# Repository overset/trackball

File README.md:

## Trackball Mezzanine PCBs

These are the mezzanine PCBs that connect the <a href="https://www.adafruit.com/product/4600">Adafruit QT Py</a> (SAMD21) MCU, <a href="https://github.com/mrjohnk/PMW3389DM">MrJohnK PMW3389</a> optical sensor breakout (<a href="https://www.tindie.com/products/jkicklighter/pmw3389-motion-sensor/">available on Tindie as of 2022</a>), simple components for the haptic feedback motor and pads for capacitive pickup wiring. This PCB allows for easy mounting inside the case for most components as well as a ground plane to help with the capacitive pickup interference. These are simple 2-layer PCBs that made with KiCad6 and includes a few custom footprints/symbols for the haptic motor. These can easily be fabricated through OSHPark, JLCPCB, etc. Original prototypes were fabricated by OSHPark and the gerber & hole files were exported from KiCad6 with OSHPark guidelines.

### Dual Optical Sensor PCB

*Currently work in progress*

This mezzanine PCB supports 2 optical sensor breakout boards being tested on a new case design. This leverages the PMW3389DM-T3QU or PMW3360DM-T2QU breakout boards from MrJohnK. Having the second optical sensor enables detecting horizontal ball movement (like a flat spin) to enable scroll/wheel events. This is specifically designed to work with the current case design detecting movements off a radial ball bearing for 1 sensor (scroll) and the trackball itself (x, y cursor movement).

<p align="center">
	<span align="left"></span>
	<span align="left"></span>
	<span align="left"></span>
	<span align="right"></span>
</p>

### Single Optical Sensor PCB

This mezzanine PCB supports a single optical sensor breakout and is good for a dedicated trackball or dedicated scrollball. This allows for a smaller case design, but made with using a 50mm or larger ball.

<p align="center">
	<span align="left"></span>
	<span align="left"></span>
	<span align="right"></span>
</p>

Assembly of the first print:

<p align="center">
	<span align="left"></span>
	<span align="left"></span>
	<span align="right"></span>
</p>

## Credits, Attribution and Inspiration

* <a href="https://github.com/monroewilliams/trackball">MonroeWilliams' Trackball</a> project
* <a href="https://github.com/jfedor2">jfedor2's multiple trackball</a> projects

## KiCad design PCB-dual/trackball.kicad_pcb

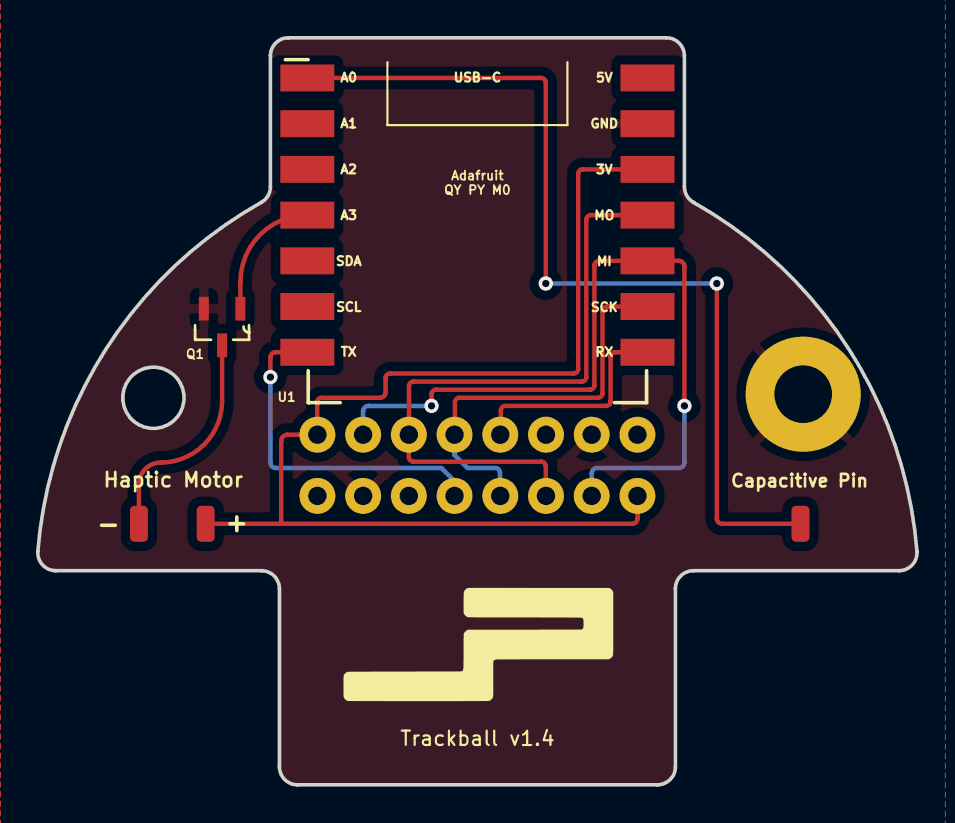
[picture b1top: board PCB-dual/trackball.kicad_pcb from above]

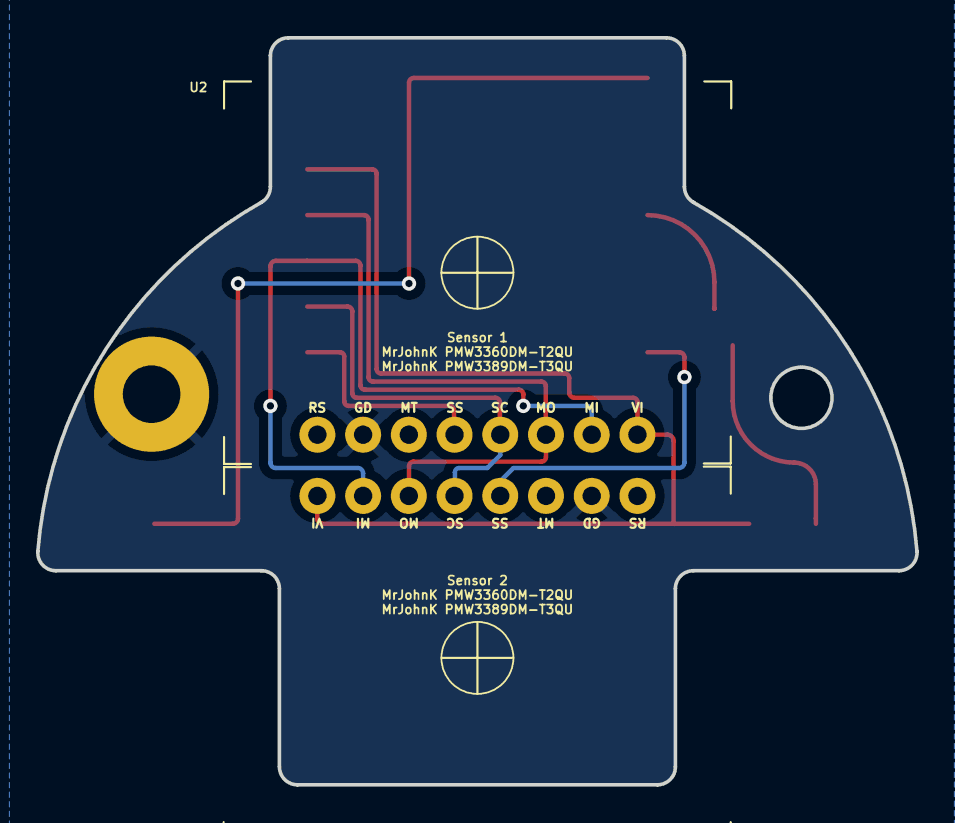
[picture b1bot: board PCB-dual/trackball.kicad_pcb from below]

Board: 2 copper layers, 48.8 x 41.5 mm, 8 parts (2 on the bottom side), 10 nets.

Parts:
+: Conn_01x01_Male; SolderWirePad_1x01_SMD_1x2mm
-: Conn_01x01_Male; SolderWirePad_1x01_SMD_1x2mm
H1: MountingHole_Pad; MountingHole_3.2mm_M3_Pad
J3: Conn_01x01_Male; SolderWirePad_1x01_SMD_1x2mm
Q1: MMBT2222A-7-F
U1: Adafruit_QT_Py_M0; Adafruit_QT_PY_M0
U2, U3: MrJohnK_PMW3360DM-T2QU

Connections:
unnamed: +.1, U1.10 (3V), U2.8 (VI), U3.8 (VI)
unnamed: -.1, Q1.3 (C)
unnamed: J3.1, U1.1 (A0)
unnamed: Q1.1 (B), U1.4 (A3)
unnamed: H1.1, Q1.2 (E), U1.9 (GND), U2.2 (GD), U3.2 (GD)
unnamed: U1.7 (TX), U3.4 (SS)
unnamed: U1.11 (MO), U2.6 (MO), U3.6 (MO)
unnamed: U1.12 (MI), U2.7 (MI), U3.7 (MI)
unnamed: U1.13 (SCK), U2.5 (SC), U3.5 (SC)
unnamed: U1.14 (RX), U2.4 (SS)

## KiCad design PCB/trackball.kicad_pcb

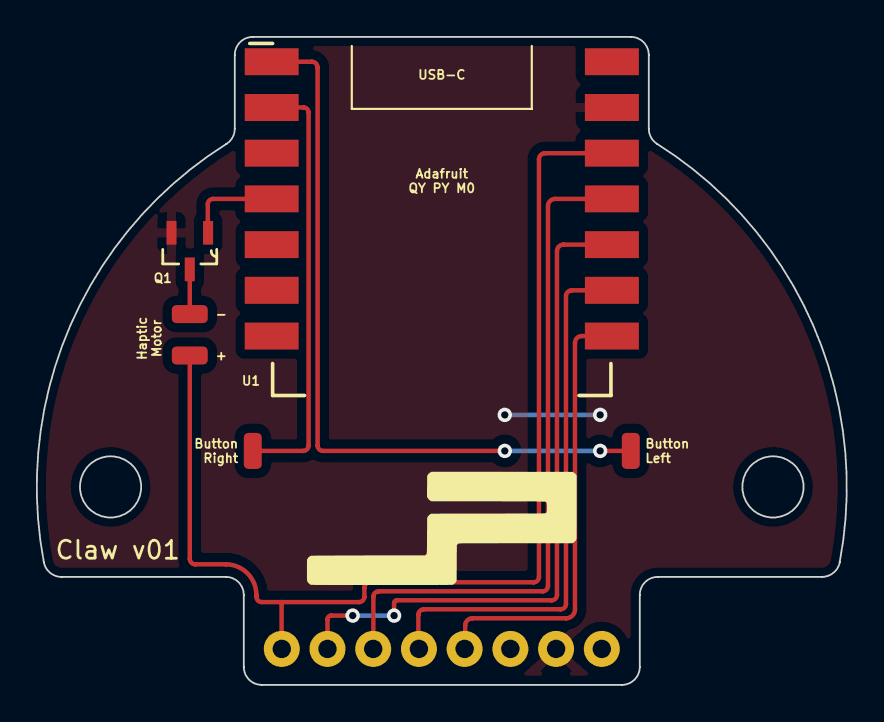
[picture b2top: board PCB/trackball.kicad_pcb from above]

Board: 2 copper layers, 45.0 x 36.0 mm, 7 parts (1 on the bottom side), 10 nets.

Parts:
+: Conn_01x01_Male; SolderWirePad_1x01_SMD_1x2mm
-: Conn_01x01_Male; SolderWirePad_1x01_SMD_1x2mm
J1, J2: Conn_01x01_Male; SolderWirePad_1x01_SMD_1x2mm
Q1: MMBT2222A-7-F
U1: Adafruit_QT_Py_M0; Adafruit_QT_PY_M0
U2: MrJohnK_PMW3360DM-T2QU

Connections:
GND: Q1.2 (E), U1.9 (GND), U2.2 (GD)
unnamed: +.1, U1.10 (3V), U2.8 (VI)
unnamed: -.1, Q1.3 (C)
unnamed: Q1.1 (B), U1.4 (A3)
unnamed: J1.1, U1.1 (A0)
unnamed: J2.1, U1.2 (A1)
unnamed: U1.11 (MO), U2.6 (MO)
unnamed: U1.12 (MI), U2.7 (MI)
unnamed: U1.13 (SCK), U2.5 (SC)
unnamed: U1.14 (RX), U2.4 (SS)

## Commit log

2022-12-16 feat: initial commit
2022-12-16 feat: added initial v01 KiCad6 project files and first pictures of mezzanine PCB
2022-12-16 feat: added v01 build pictures with mezzanine PCB, QT Py and PMW3389 breakout
2022-12-16 bug: capacitive pickup, not haptic pickup
2022-12-17 docs: tweak table for image scaling
2022-12-17 docs: added links to breakouts, attributions and dual vs single PCB outline
2022-12-17 feat: move PCB to PCB-single to differentiate single vs dual sensor PCBs
2022-12-17 docs: add more details for included gerbers and OSHPark preferences
2022-12-18 feat: add WIP for dual sensor PCB. Edge cut works with current 3D model geometry, footprints updated with more silkscreen adds. Just about to begin re-wiring the pads.
2022-12-18 feat: first draft of v02 trackball with dual sensor support, fixes to footprints and OSHPark gerber .zip not yet tested
2022-12-18 docs: quick intro with images for the draft dual sensor mezzanine PCB
2022-12-19 docs: typos on breakout boards sensor IDs
2022-12-19 feat: cleaned up tracks minimizing crossover on F/B layers, simplified some tracks, ground plane now on both sides
2022-12-19 docs: updated v02 PCB editor view and 3D front/back images
2022-12-19 docs: dual sensor to the top of the list
2022-12-19 docs: nuke github html table borders
2022-12-19 docs: nuke github html table borders attempt #2
2022-12-19 docs: cleaner markdown+html grid and renamed dual sensor pictures to correct timestamp
2022-12-19 docs: make the img's float correctly
2022-12-19 docs: center the floating image grids
2022-12-21 feat: added 3D models for QT Py and diode to existing project footprints
2022-12-21 bug: add .step files for updated footprints
2022-12-21 feat: new v03 with new mounting hole placement and proper placement of second sensor with fitment in 55mm sphere sized case
2022-12-21 feat: tweak to silkscreen
2022-12-21 docs: added v03 dual sensor docs, step file from KiCad6
2022-12-21 feat: new gerbers for v03 of dual sensor PCB
2022-12-21 feat: v03 dual sensor PCB OSHPark gerber .zip
2023-01-01 feat: v1.4 with ~3.4mm spacing between sensor header pins on center with new case optimization, QTPy positioning fix, new ground pad for grounding to case, few track tweaks
2023-01-01 feat: v1.4 gerbers and drill files for OSHPark
2023-01-01 feat: v1.4 OSHPark gerber + drill zip
2023-01-27 docs: add quick video on reflow soldering SMD parts (QT Py and transistor) onto the v1.4 dual sensor PCB
2023-01-27 docs: add new v1.4 dual sensor PCB KiCAD images
2023-01-27 docs: fix v1.4 PCB editor picture to be same aspect ratio as 3D view
2023-04-25 feat: updated PCB to KiCad 7

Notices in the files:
PCB-dual/trackball.kicad_pcb:
License: MIT
